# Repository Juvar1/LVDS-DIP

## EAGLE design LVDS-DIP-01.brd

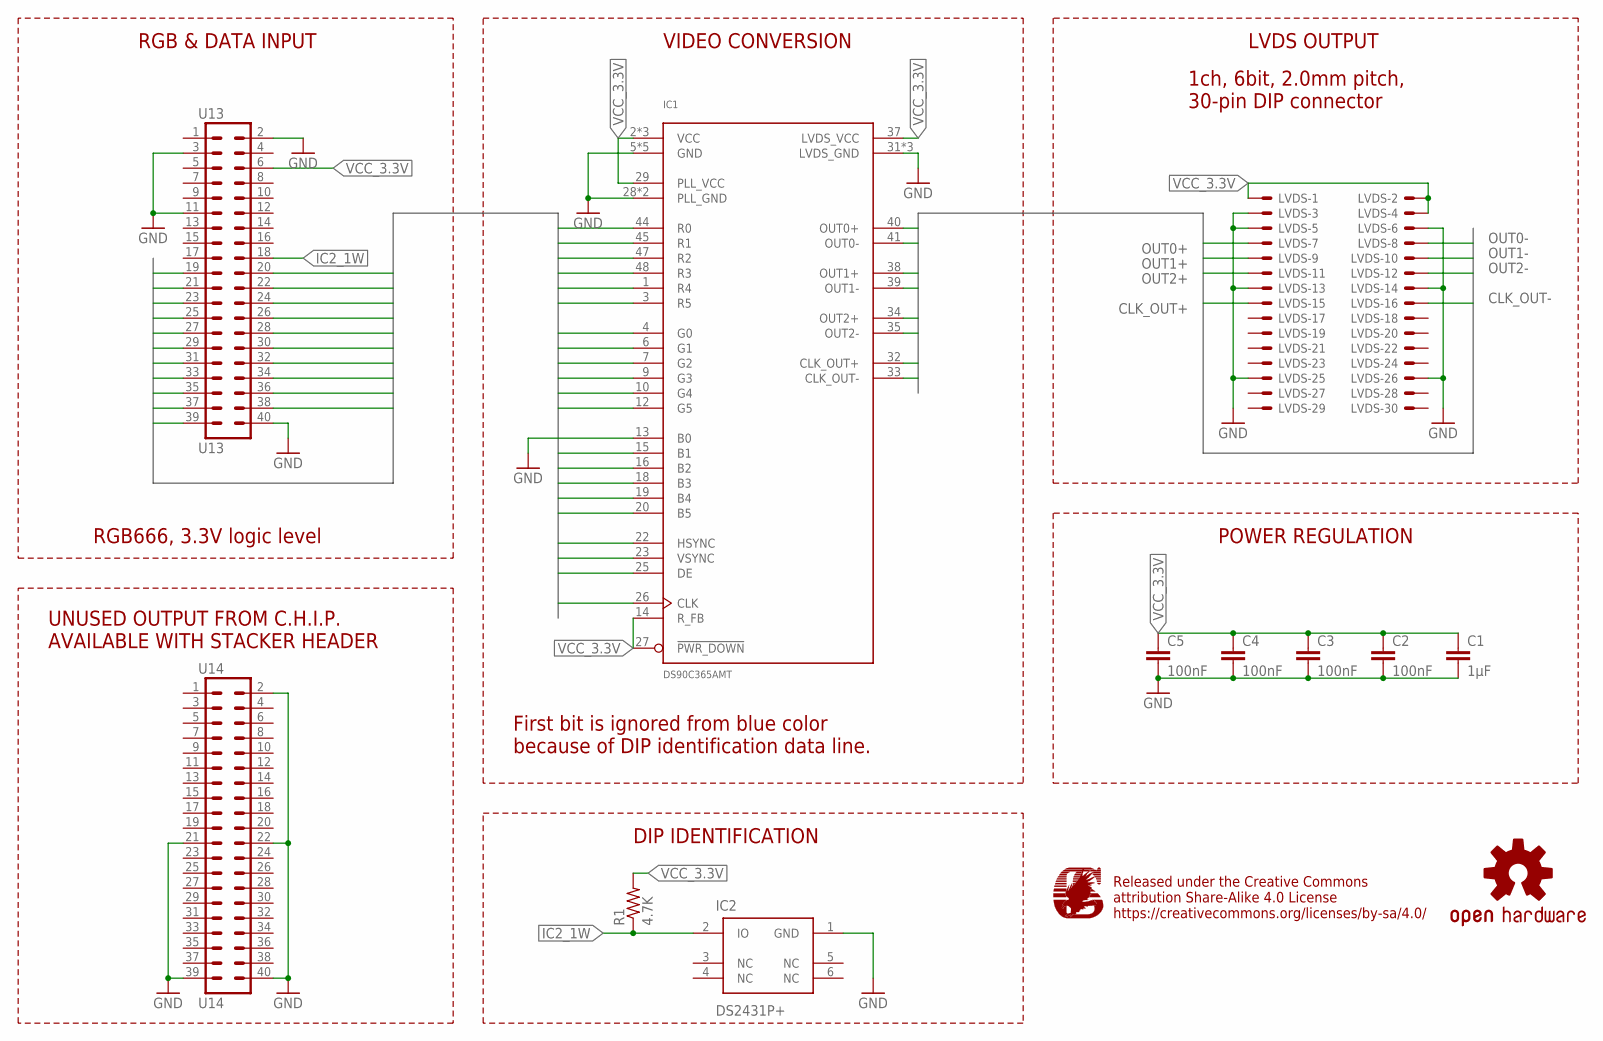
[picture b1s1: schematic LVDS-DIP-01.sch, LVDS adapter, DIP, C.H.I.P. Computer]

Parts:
C1: 1µF; 0603-CAP
C2, C3, C4, C5: 100nF; 0603-CAP
IC1: DS90C365AMT; TSSOP48
IC2: DS2431P+; DS2431P+T&R
LOGO1: OSHW-LOGOM; OSHW-LOGO-M
LVDS: 332-30
R1: 4.7K; 0603-RES
U13: U13; 2X20
U14: U14; 2X20

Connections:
B1: IC1.15 (B1), U13.19
B2: IC1.16 (B2), U13.20
B3: IC1.18 (B3), U13.21
B4: IC1.19 (B4), U13.22
B5: IC1.20 (B5), U13.23
CLK: IC1.26 (CLK), U13.36
CLK_OUT+: IC1.32 (CLK_OUT+), LVDS.15
CLK_OUT-: IC1.33 (CLK_OUT-), LVDS.16
DE: IC1.25 (DE), U13.39
G0: IC1.4 (G0), U13.24
G1: IC1.6 (G1), U13.25
G2: IC1.7 (G2), U13.26
G3: IC1.9 (G3), U13.27
G4: IC1.10 (G4), U13.28
G5: IC1.12 (G5), U13.29
GND: C1.2, C2.2, C3.2, C4.2, C5.2, IC1.5 (GND), IC1.11 (GND), IC1.13 (B0), IC1.17 (GND), IC1.24 (GND), IC1.28 (PLL_GND), IC1.30 (PLL_GND), IC1.31 (LVDS_GND), IC1.36 (LVDS_GND), IC1.42 (LVDS_GND), IC1.46 (GND), IC2.1 (GND), LVDS.3, LVDS.5, LVDS.6, LVDS.13, LVDS.14, LVDS.25, LVDS.26, U13.2, U13.3, U13.11, U13.40, U14.2, U14.21, U14.22, U14.39, U14.40
HSYNC: IC1.22 (HSYNC), U13.37
IC2_1W: IC2.2 (IO), R1.1, U13.18
OUT0+: IC1.40 (OUT0+), LVDS.7
OUT0-: IC1.41 (OUT0-), LVDS.8
OUT1+: IC1.38 (OUT1+), LVDS.9
OUT1-: IC1.39 (OUT1-), LVDS.10
OUT2+: IC1.34 (OUT2+), LVDS.11
OUT2-: IC1.35 (OUT2-), LVDS.12
R0: IC1.44 (R0), U13.30
R1: IC1.45 (R1), U13.31
R2: IC1.47 (R2), U13.32
R3: IC1.48 (R3), U13.33
R4: IC1.1 (R4), U13.34
R5: IC1.3 (R5), U13.35
VCC_3.3V: C1.1, C2.1, C3.1, C4.1, C5.1, IC1.2 (VCC), IC1.8 (VCC), IC1.14 (R_FB), IC1.21 (VCC), IC1.27 (!PWR_DOWN!), IC1.29 (PLL_VCC), IC1.37 (LVDS_VCC), LVDS.1, LVDS.2, LVDS.4, R1.2, U13.6
VSYNC: IC1.23 (VSYNC), U13.38

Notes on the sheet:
POWER REGULATION
First bit is ignored from blue color because of DIP identification data line.
Released under the Creative Commons attribution Share-Alike 4.0 License https://creativecommons.org/licenses/by-sa/4.0/
LVDS OUTPUT
VIDEO CONVERSION
RGB & DATA INPUT
UNUSED OUTPUT FROM C.H.I.P. AVAILABLE WITH STACKER HEADER
DIP IDENTIFICATION
RGB666, 3.3V logic level
1ch, 6bit, 2.0mm pitch, 30-pin DIP connector

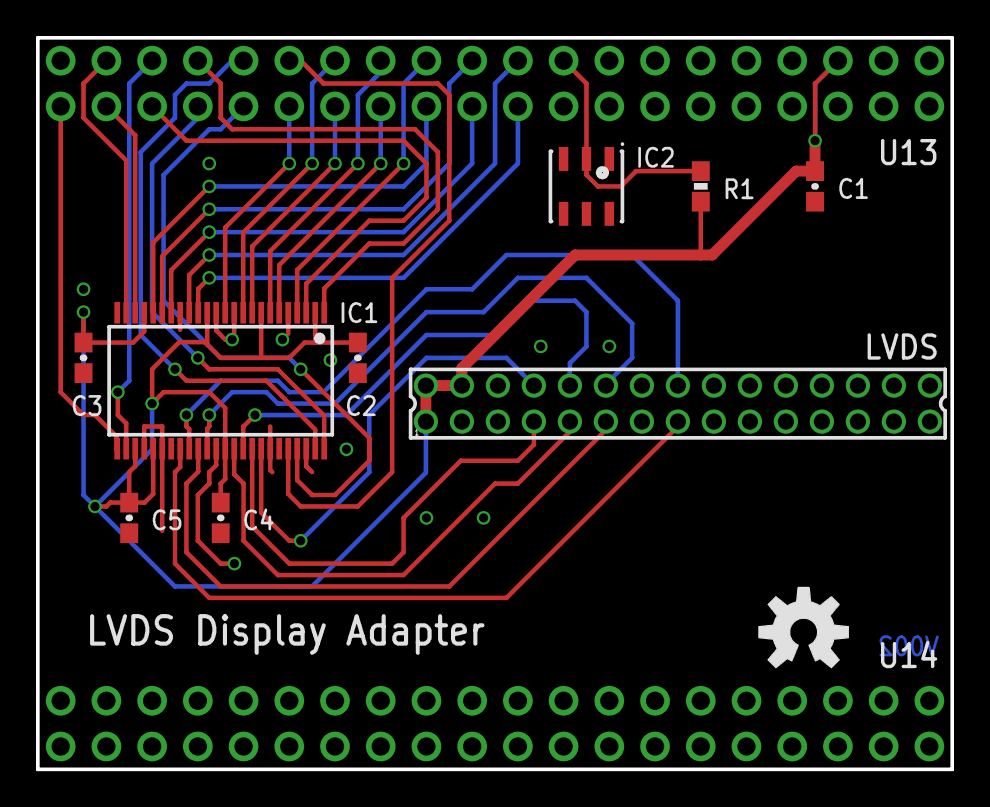
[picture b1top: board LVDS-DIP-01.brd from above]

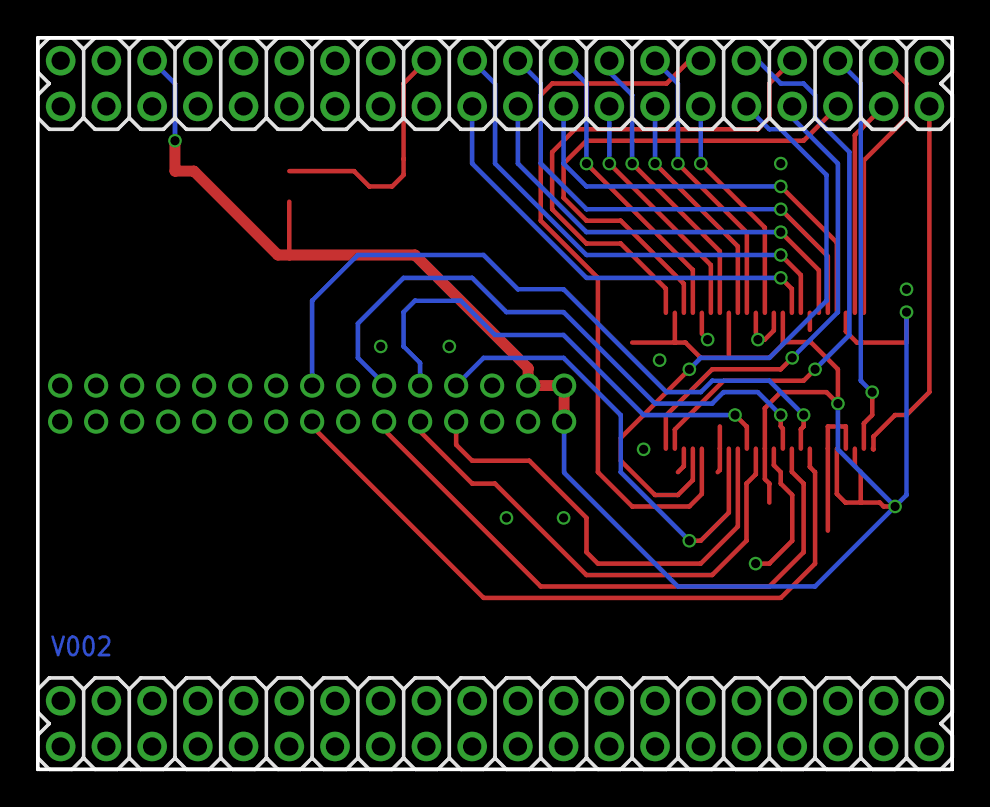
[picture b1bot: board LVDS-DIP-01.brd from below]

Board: 2 copper layers, 50.8 x 40.6 mm, 12 parts (2 on the bottom side), 32 nets.

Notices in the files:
parts and their libraries:
SparkFun-Aesthetics: Licensing: Creative Commons ShareAlike 4.0 International - https://creativecommons.org/licenses/by-sa/4.0
